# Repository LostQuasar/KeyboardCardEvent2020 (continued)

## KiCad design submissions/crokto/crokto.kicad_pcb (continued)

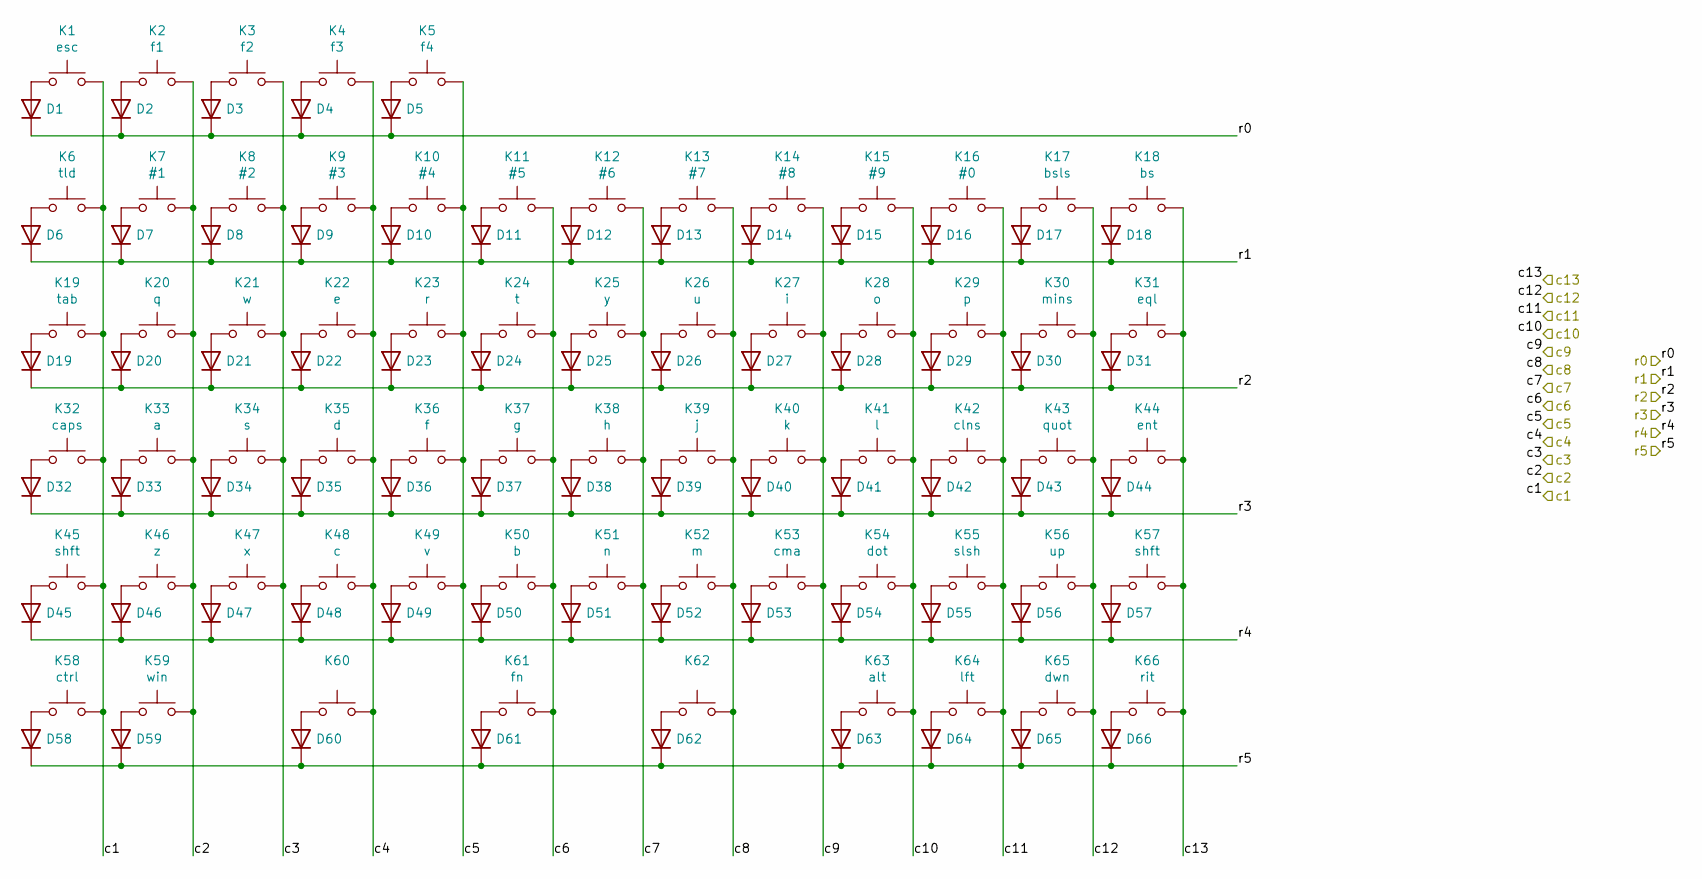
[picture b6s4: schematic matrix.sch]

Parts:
D1, D2, D3, D4, D5, D6, D7, D8, D9, D10, D11, D12, D13, D14, D15, D16, D17, D18, D19, D20, D21, D22, D23, D24, D25, D26, D27, D28, D29, D30, D31, D32, D33, D34, D35, D36, D37, D38, D39, D40, D41, D42, D43, D44, D45, D46, D47, D48, D49, D50, D51, D52, D53, D54, D55, D56, D57, D58, D59, D60, D61, D62, D63, D64, D65, D66: D; D_SOD-323F-VIA; lcsc C2128
K1: esc; 100; lcsc C318887
K2: f1; 100; lcsc C318887
K3: f2; 100; lcsc C318887
K4: f3; 100; lcsc C318887
K5: f4; 100; lcsc C318887
K6: tld; 100; lcsc C318887
K7: #1; 100; lcsc C318887
K8: #2; 100; lcsc C318887
K9: #3; 100; lcsc C318887
K10: #4; 100; lcsc C318887
K11: #5; 100; lcsc C318887
K12: #6; 100; lcsc C318887
K13: #7; 100; lcsc C318887
K14: #8; 100; lcsc C318887
K15: #9; 100; lcsc C318887
K16: #0; 100; lcsc C318887
K17: bsls; 100; lcsc C318887
K18: bs; 100; lcsc C318887
K19: tab; 100; lcsc C318887
K20: q; 100; lcsc C318887
K21: w; 100; lcsc C318887
K22: e; 100; lcsc C318887
K23: r; 100; lcsc C318887
K24: t; 100; lcsc C318887
K25: y; 100; lcsc C318887
K26: u; 100; lcsc C318887
K27: i; 100; lcsc C318887
K28: o; 100; lcsc C318887
K29: p; 100; lcsc C318887
K30: mins; 100; lcsc C318887
K31: eql; 100; lcsc C318887
K32: caps; 100; lcsc C318887
K33: a; 100; lcsc C318887
K34: s; 100; lcsc C318887
K35: d; 100; lcsc C318887
K36: f; 100; lcsc C318887
K37: g; 100; lcsc C318887
K38: h; 100; lcsc C318887
K39: j; 100; lcsc C318887
K40: k; 100; lcsc C318887
K41: l; 100; lcsc C318887
K42: clns; 100; lcsc C318887
K43: quot; 100; lcsc C318887
K44: ent; 100; lcsc C318887
K45, K57: shft; 100; lcsc C318887
K46: z; 100; lcsc C318887
K47: x; 100; lcsc C318887
K48: c; 100; lcsc C318887
K49: v; 100; lcsc C318887
K50: b; 100; lcsc C318887
K51: n; 100; lcsc C318887
K52: m; 100; lcsc C318887
K53: cma; 100; lcsc C318887
K54: dot; 100; lcsc C318887
K55: slsh; 100; lcsc C318887
K56: up; 100; lcsc C318887
K58: ctrl; 100; lcsc C318887
K59: win; 150; lcsc C318887
K60, K62: 200; lcsc C318887
K61: fn; 200; lcsc C318887
K63: alt; 150; lcsc C318887
K64: lft; 100; lcsc C318887
K65: dwn; 100; lcsc C318887
K66: rit; 100; lcsc C318887

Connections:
/16u2/B1: K18.2, K31.2, K44.2, K57.2, K66.2; also elsewhere on the board
/16u2/B2: K12.2, K25.2, K38.2, K51.2; also elsewhere on the board
/16u2/B3: K11.2, K24.2, K37.2, K50.2, K61.2; also elsewhere on the board
/16u2/B4: K5.2, K10.2, K23.2, K36.2, K49.2; also elsewhere on the board
/16u2/B5: K4.2, K9.2, K22.2, K35.2, K48.2, K60.2; also elsewhere on the board
/16u2/B6: K3.2, K8.2, K21.2, K34.2, K47.2; also elsewhere on the board
/16u2/B7: K2.2, K7.2, K20.2, K33.2, K46.2, K59.2; also elsewhere on the board
/16u2/C2: K15.2, K28.2, K41.2, K54.2, K63.2; also elsewhere on the board
/16u2/C4: K14.2, K27.2, K40.2, K53.2; also elsewhere on the board
/16u2/C5: K13.2, K26.2, K39.2, K52.2, K62.2; also elsewhere on the board
/16u2/C6: D1.1 (K), D2.1 (K), D3.1 (K), D4.1 (K), D5.1 (K); also elsewhere on the board
/16u2/C7: K1.2, K6.2, K19.2, K32.2, K45.2, K58.2; also elsewhere on the board
/16u2/D0: K16.2, K29.2, K42.2, K55.2, K64.2; also elsewhere on the board
/16u2/D1: K17.2, K30.2, K43.2, K56.2, K65.2; also elsewhere on the board
/16u2/D2: D6.1 (K), D7.1 (K), D8.1 (K), D9.1 (K), D10.1 (K), D11.1 (K), D12.1 (K), D13.1 (K), D14.1 (K), D15.1 (K), D16.1 (K), D17.1 (K), D18.1 (K); also elsewhere on the board
/16u2/D3: D19.1 (K), D20.1 (K), D21.1 (K), D22.1 (K), D23.1 (K), D24.1 (K), D25.1 (K), D26.1 (K), D27.1 (K), D28.1 (K), D29.1 (K), D30.1 (K), D31.1 (K); also elsewhere on the board
/16u2/D4: D32.1 (K), D33.1 (K), D34.1 (K), D35.1 (K), D36.1 (K), D37.1 (K), D38.1 (K), D39.1 (K), D40.1 (K), D41.1 (K), D42.1 (K), D43.1 (K), D44.1 (K); also elsewhere on the board
/16u2/D5: D45.1 (K), D46.1 (K), D47.1 (K), D48.1 (K), D49.1 (K), D50.1 (K), D51.1 (K), D52.1 (K), D53.1 (K), D54.1 (K), D55.1 (K), D56.1 (K), D57.1 (K); also elsewhere on the board
/16u2/D6: D58.1 (K), D59.1 (K), D60.1 (K), D61.1 (K), D62.1 (K), D63.1 (K), D64.1 (K), D65.1 (K), D66.1 (K); also elsewhere on the board
unnamed: D1.2 (A), K1.1
unnamed: D2.2 (A), K2.1
unnamed: D3.2 (A), K3.1
unnamed: D4.2 (A), K4.1
unnamed: D5.2 (A), K5.1
unnamed: D6.2 (A), K6.1
unnamed: D7.2 (A), K7.1
unnamed: D8.2 (A), K8.1
unnamed: D9.2 (A), K9.1
unnamed: D10.2 (A), K10.1
unnamed: D11.2 (A), K11.1
unnamed: D12.2 (A), K12.1
unnamed: D13.2 (A), K13.1
unnamed: D14.2 (A), K14.1
unnamed: D15.2 (A), K15.1
unnamed: D16.2 (A), K16.1
unnamed: D17.2 (A), K17.1
unnamed: D18.2 (A), K18.1
unnamed: D19.2 (A), K19.1
unnamed: D20.2 (A), K20.1
unnamed: D21.2 (A), K21.1
unnamed: D22.2 (A), K22.1
unnamed: D23.2 (A), K23.1
unnamed: D24.2 (A), K24.1
unnamed: D25.2 (A), K25.1
unnamed: D26.2 (A), K26.1
unnamed: D27.2 (A), K27.1
unnamed: D28.2 (A), K28.1
unnamed: D29.2 (A), K29.1
unnamed: D30.2 (A), K30.1
unnamed: D31.2 (A), K31.1
unnamed: D32.2 (A), K32.1
unnamed: D33.2 (A), K33.1
unnamed: D34.2 (A), K34.1
unnamed: D35.2 (A), K35.1
unnamed: D36.2 (A), K36.1
unnamed: D37.2 (A), K37.1
unnamed: D38.2 (A), K38.1
unnamed: D39.2 (A), K39.1
unnamed: D40.2 (A), K40.1
unnamed: D41.2 (A), K41.1
unnamed: D42.2 (A), K42.1
unnamed: D43.2 (A), K43.1
unnamed: D44.2 (A), K44.1
unnamed: D45.2 (A), K45.1
unnamed: D46.2 (A), K46.1
unnamed: D47.2 (A), K47.1
unnamed: D48.2 (A), K48.1
unnamed: D49.2 (A), K49.1
unnamed: D50.2 (A), K50.1
unnamed: D51.2 (A), K51.1
unnamed: D52.2 (A), K52.1
unnamed: D53.2 (A), K53.1
unnamed: D54.2 (A), K54.1
unnamed: D55.2 (A), K55.1
unnamed: D56.2 (A), K56.1
unnamed: D57.2 (A), K57.1
unnamed: D58.2 (A), K58.1
unnamed: D59.2 (A), K59.1
unnamed: D60.2 (A), K60.1
unnamed: D61.2 (A), K61.1
unnamed: D62.2 (A), K62.1
unnamed: D63.2 (A), K63.1
unnamed: D64.2 (A), K64.1
unnamed: D65.2 (A), K65.1
unnamed: D66.2 (A), K66.1

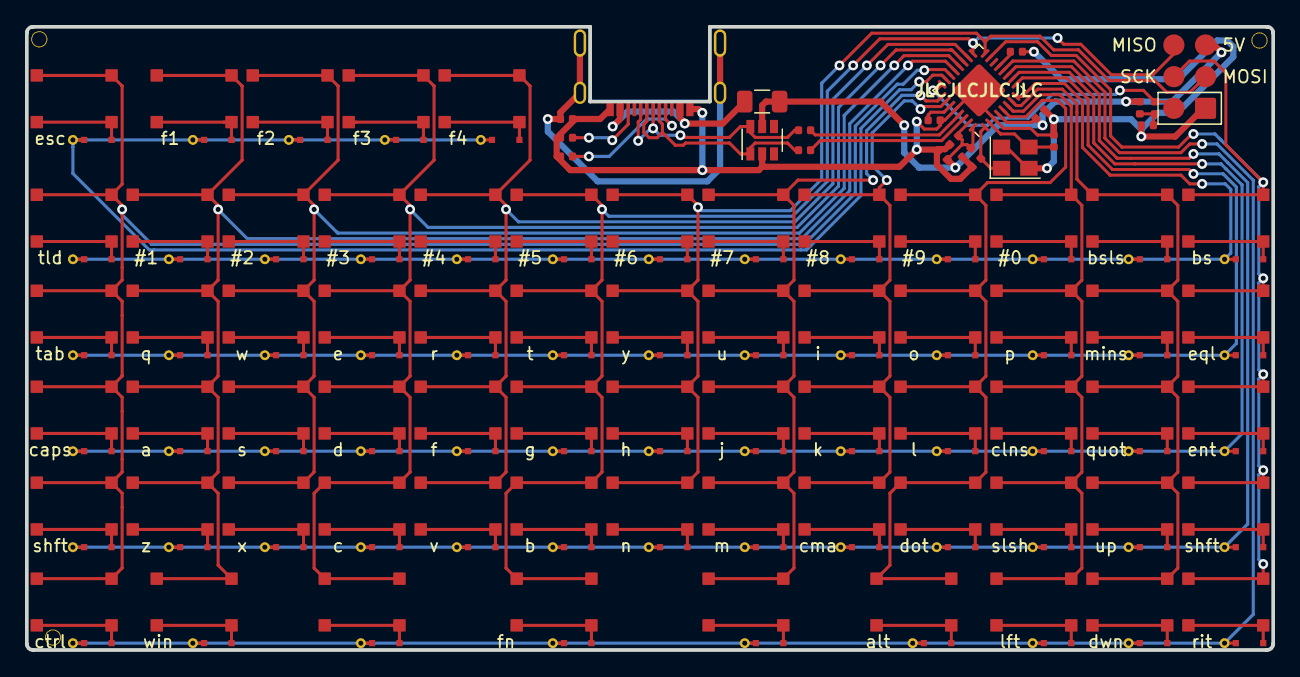
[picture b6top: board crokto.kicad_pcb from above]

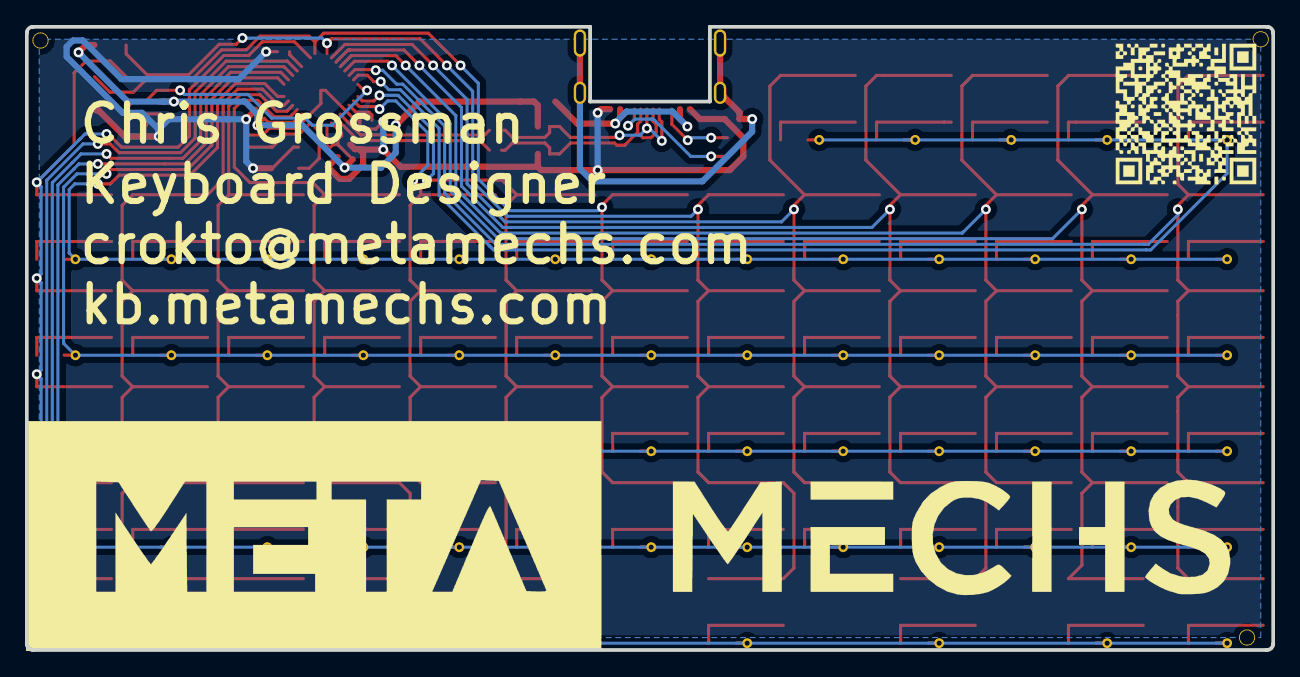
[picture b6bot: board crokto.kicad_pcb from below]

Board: 2 copper layers, 100.0 x 50.0 mm, 160 parts (2 on the bottom side), 101 nets.

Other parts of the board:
C1: 10u; C_0402_1005Metric
C2, C3, C4, C8: 100n; C_0402_1005Metric
C5, C6: 10pf; C_0402_1005Metric
C7: 1u; C_0402_1005Metric
H3: jlc
H4, H5, H6: jlc; JLCPCBA
J1: AVR-ISP-6; 2x3-jumper
R1, R2: 22; R_0402_1005Metric
R3: 4.7K; R_0402_1005Metric
R4: 330; R_0402_1005Metric
R5: 10k; R_0402_1005Metric
U1: ATmega16U2-MU; QFN-32-1EP_5x5mm_P0.5mm_EP3.1x3.1mm
Y1: Crystal_GND24; Crystal_SMD_3225-4Pin_3.2x2.5mm

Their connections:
+5V: C1.1, C2.1, C3.1, C4.1, J1.2, R3.2, U1.4, U1.31, U1.32; also elsewhere on the board
/16u2/B1: J1.3, U1.15; also elsewhere on the board
/16u2/B2: J1.4, U1.16; also elsewhere on the board
/16u2/B3: J1.1, U1.17; also elsewhere on the board
/16u2/B4: U1.18; also elsewhere on the board
/16u2/B5: U1.19; also elsewhere on the board
/16u2/B6: U1.20; also elsewhere on the board
/16u2/B7: U1.21; also elsewhere on the board
/16u2/C2: U1.5; also elsewhere on the board
/16u2/C4: U1.26; also elsewhere on the board
/16u2/C5: U1.25; also elsewhere on the board
/16u2/C6: U1.23; also elsewhere on the board
/16u2/C7: U1.22; also elsewhere on the board
/16u2/D0: U1.6; also elsewhere on the board
/16u2/D1: U1.7; also elsewhere on the board
/16u2/D2: U1.8; also elsewhere on the board
/16u2/D3: U1.9; also elsewhere on the board
/16u2/D4: U1.10; also elsewhere on the board
/16u2/D5: U1.11; also elsewhere on the board
/16u2/D6: U1.12; also elsewhere on the board
/16u2/D+: R1.1, U1.29
/16u2/D-: R2.2, U1.30
/16u2/DB+: R1.2; also elsewhere on the board
/16u2/DB-: R2.1; also elsewhere on the board
/16u2/RST: J1.5, R4.2, U1.24
GND: C1.2, C2.2, C3.2, C4.2, C5.2, C6.2, C7.2, C8.2, J1.6, R5.2, U1.3, U1.28, U1.33, Y1.2, Y1.4; also elsewhere on the board
unnamed: C5.1, U1.1, Y1.1
unnamed: C6.1, U1.2, Y1.3
unnamed: C7.1, U1.27
unnamed: C8.1, R3.1, R4.1
unnamed: R5.1, U1.13

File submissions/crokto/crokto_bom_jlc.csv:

"Comment","Designator","Footprint","LCSC Part #"
"10u","C1","C_0402_1005Metric","C15525"
"100n","C2,C3,C4,C8","C_0402_1005Metric","C1525"
"10pf","C5,C6","C_0402_1005Metric","C32949"
"1u","C7","C_0402_1005Metric","C52923"
"D","D6,D19,D32,D45,D58,D7,D20,D33,D46,D59,D8,D21,D34,D47,D9,D22,D35,D48,D60,D10,D23,D36,D49,D11,D24,D37,D50,D61,D12,D25,D38,D51,D13,D26,D39,D52,D62,D14,D27,D40,D53,D15,D28,D41,D54,D63,D16,D29,D42,D55,D64,D17,D30,D43,D56,D65,D18,D31,D44,D57,D66,D1,D2,D3,D4,D5","D_SOD-323F-VIA","C2128"
"esc","K1","100","C318887"
"f1","K2","100","C318887"
"f2","K3","100","C318887"
"f3","K4","100","C318887"
"f4","K5","100","C318887"
"tld","K6","100","C318887"
"#1","K7","100","C318887"
"#2","K8","100","C318887"
"#3","K9","100","C318887"
"#4","K10","100","C318887"
"#5","K11","100","C318887"
"#6","K12","100","C318887"
"#7","K13","100","C318887"
"#8","K14","100","C318887"
"#9","K15","100","C318887"
"#0","K16","100","C318887"
"bsls","K17","100","C318887"
"bs","K18","100","C318887"
"tab","K19","100","C318887"
"q","K20","100","C318887"
"w","K21","100","C318887"
"e","K22","100","C318887"
"r","K23","100","C318887"
"t","K24","100","C318887"
"y","K25","100","C318887"
"u","K26","100","C318887"
"i","K27","100","C318887"
"o","K28","100","C318887"
"p","K29","100","C318887"
"mins","K30","100","C318887"
"eql","K31","100","C318887"
"caps","K32","100","C318887"
"a","K33","100","C318887"
"s","K34","100","C318887"
"d","K35","100","C318887"
"f","K36","100","C318887"
"g","K37","100","C318887"
"h","K38","100","C318887"
"j","K39","100","C318887"
"k","K40","100","C318887"
"l","K41","100","C318887"
"clns","K42","100","C318887"
"quot","K43","100","C318887"
"ent","K44","100","C318887"
"shft","K45,K57","100","C318887"
"z","K46","100","C318887"
"x","K47","100","C318887"
"c","K48","100","C318887"
"v","K49","100","C318887"
"b","K50","100","C318887"
"n","K51","100","C318887"
"m","K52","100","C318887"
"cma","K53","100","C318887"
"dot","K54","100","C318887"
"slsh","K55","100","C318887"
"up","K56","100","C318887"
"ctrl","K58","100","C318887"
"win","K59","150","C318887"
"","K60,K62","200","C318887"
"fn","K61","200","C318887"
"alt","K63","150","C318887"
"lft","K64","100","C318887"
"dwn","K65","100","C318887"
"rit","K66","100","C318887"
"PTC","PTC1","Fuse_1206_3216Metric","C70076"
"22","R1,R2","R_0402_1005Metric","C25092"
"4.7K","R3","R_0402_1005Metric","C25900"
"330","R4","R_0402_1005Metric","C25890"
"10k","R5","R_0402_1005Metric","C25744"
"5.1k","R7,R8","R_0402_1005Metric","C25905"
"0","R9","R_0402_1005Metric","C25905"
"ATmega16U2-MU","U1","QFN-32-1EP_5x5mm_P0.5mm_EP3.1x3.1mm","C17317"
"SRV05-4","U2","SOT-23-6","C85364"
"Crystal_GND24","Y1","Crystal_SMD_3225-4Pin_3.2x2.5mm","C13738"

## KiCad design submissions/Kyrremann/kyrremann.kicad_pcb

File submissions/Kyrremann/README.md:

# Kyrremann's Business card

This is my business card aka the keychuks! The keyboard can be split in two, and connected with 6 individual wires to
form a split board, or used as nunchuks when you're bored.

The inital idea was to try my hands at a split board, but the size made it a bit too hard for me, so instead I went
with something between. Where you can split it, but you have to make your own 6 pin wire, and solder it.

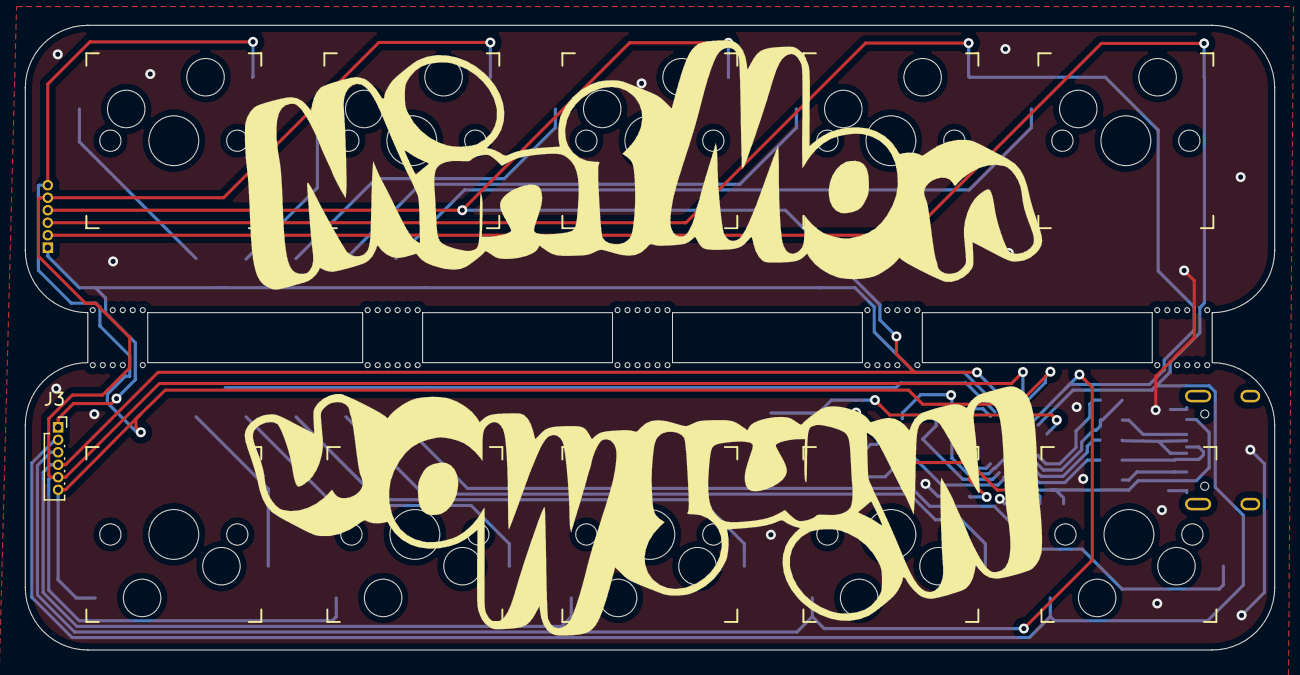
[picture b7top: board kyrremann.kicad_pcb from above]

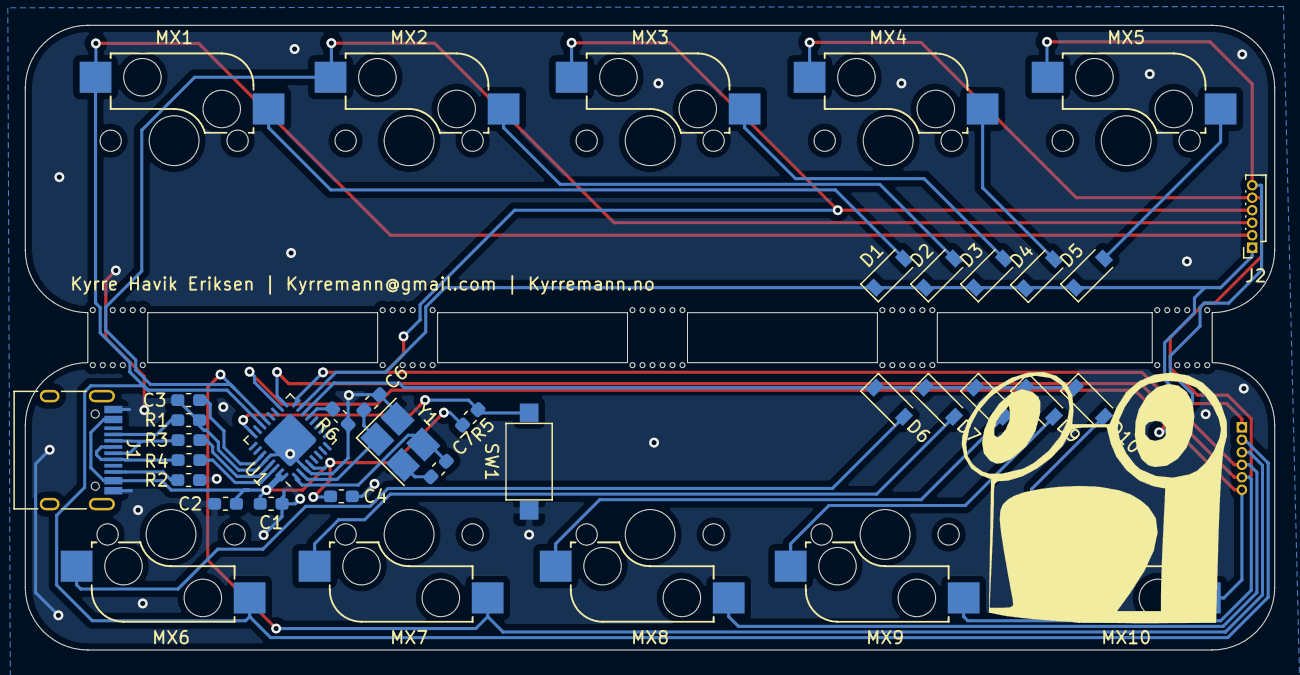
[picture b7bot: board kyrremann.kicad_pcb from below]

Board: 2 copper layers, 100.0 x 50.0 mm, 38 parts (27 on the bottom side), 30 nets.

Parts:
C1, C2, C3: 1uF; C_0603_1608Metric_Pad1.05x0.95mm_HandSolder
C4: 0.1uF; C_0603_1608Metric_Pad1.05x0.95mm_HandSolder
C6, C7: 14pF; C_0603_1608Metric_Pad1.05x0.95mm_HandSolder
D1, D2, D3, D4, D5, D6, D7, D8, D9, D10: D; D_SOD-123
J1: USB_C_Receptacle_USB2.0; USB_C_Receptacle_HRO_TYPE-C-31-M-12
J2, J3: Conn_01x06_Female; PinSocket_1x06_P1.00mm_Vertical
MX1, MX2, MX3, MX4, MX5, MX6, MX7, MX8, MX9, MX10: MX-NoLED; Kailh_socket_MX
R1, R2: 5.1K; R_0603_1608Metric_Pad1.05x0.95mm_HandSolder
R3, R4: 22; R_0603_1608Metric_Pad1.05x0.95mm_HandSolder
R5, R6: 10K; R_0603_1608Metric_Pad1.05x0.95mm_HandSolder
SW1: SW_Push; SW_SPST_CK_RS282G05A3
U1: ATmega32U2-MU; QFN-32-1EP_5x5mm_P0.5mm_EP3.1x3.1mm
Y1: 16Mhz; Crystal_SMD_3225-4Pin_3.2x2.5mm_HandSoldering

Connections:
/+5v: C1.1, C2.1, C4.1, J1.A4, J1.A9, J1.B4, J1.B9, R5.2, U1.4, U1.31, U1.32
/COL00: J2.2, J3.2, MX1.1, MX6.1, U1.22
/COL01: J2.3, J3.3, MX2.1, MX7.1, U1.21
/COL02: J2.4, J3.4, MX3.1, MX8.1, U1.16
/COL03: J2.5, J3.5, MX4.1, MX9.1, U1.17
/COL04: J2.6, J3.6, MX5.1, MX10.1, U1.18
/D+: J1.A6, J1.B6, R4.1
/D-: J1.A7, J1.B7, R3.2
/RESET: R5.1, SW1.1, U1.24
/ROW0: D1.1, D2.1, D3.1, D4.1, D5.1, J2.1, J3.1, U1.15
/ROW1: D6.1, D7.1, D8.1, D9.1, D10.1, U1.14
/UCAP: C3.1, U1.27
/XTAL1: C7.1, U1.1, Y1.3
/XTAL2: C6.1, U1.2, Y1.1
GND: C1.2, C2.2, C3.2, C4.2, C6.2, C7.2, J1.A1, J1.A12, J1.B1, J1.B12, R1.1, R2.2, R6.1, SW1.2, U1.3, U1.28, U1.33, Y1.2, Y1.4
unnamed: D1.2, MX1.2
unnamed: D2.2, MX2.2
unnamed: D3.2, MX3.2
unnamed: D4.2, MX4.2
unnamed: D5.2, MX5.2
unnamed: D6.2, MX6.2
unnamed: D7.2, MX7.2
unnamed: D8.2, MX8.2
unnamed: D9.2, MX9.2
unnamed: D10.2, MX10.2
unnamed: J1.A5, R1.2
unnamed: J1.B5, R2.1
unnamed: R3.1, U1.29
unnamed: R4.2, U1.30
unnamed: R6.2, U1.13

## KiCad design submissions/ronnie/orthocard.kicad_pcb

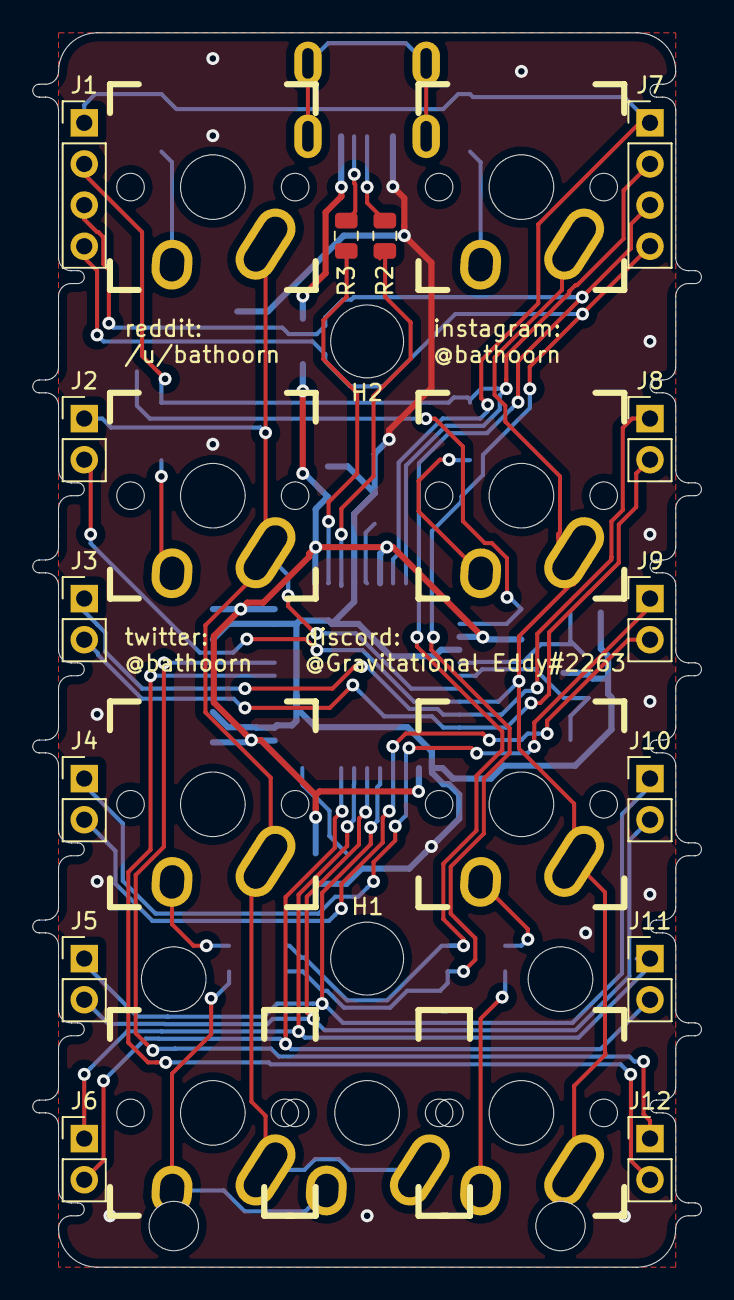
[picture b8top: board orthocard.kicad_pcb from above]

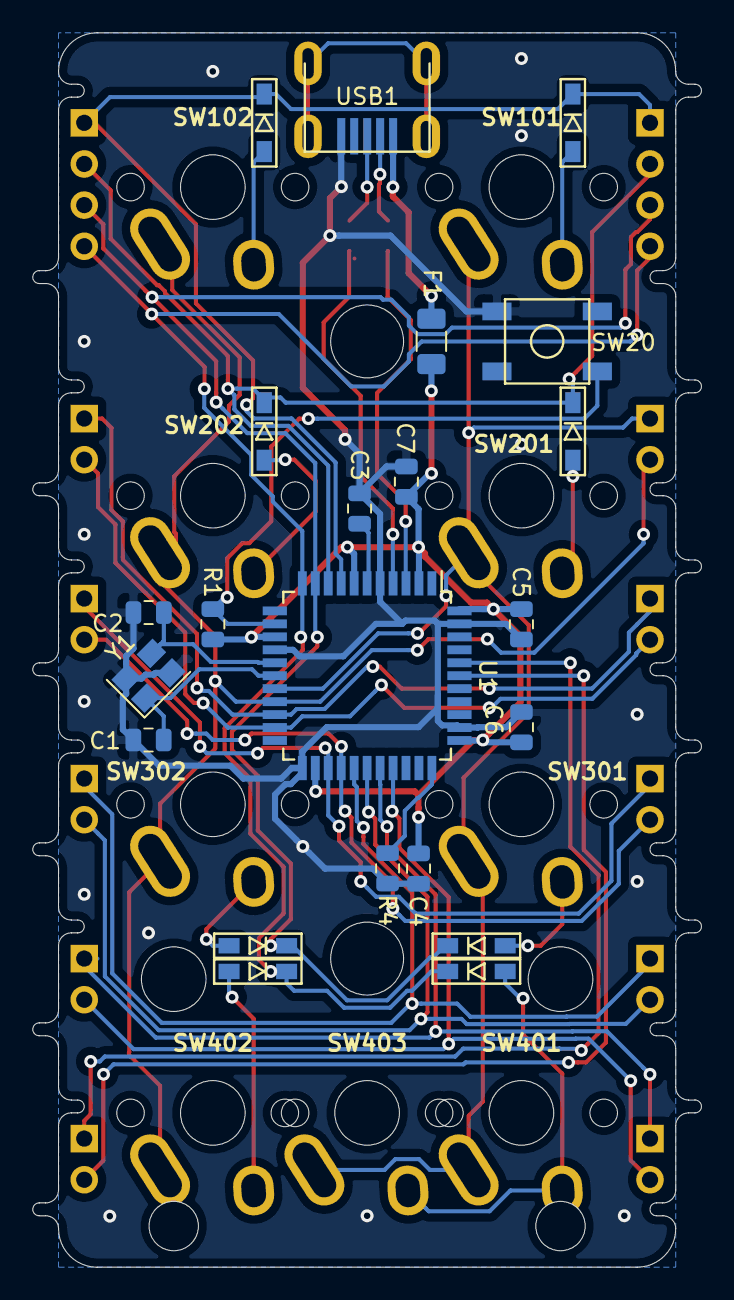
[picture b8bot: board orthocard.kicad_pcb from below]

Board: 2 copper layers, 41.3 x 76.2 mm, 47 parts (14 on the bottom side), 36 nets.

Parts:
C1, C2: 22pF; C_0805_2012Metric
C3: 1uF; C_0805_2012Metric
C4, C5, C6: 0.1uF; C_0805_2012Metric
C7: 10uF; C_0805_2012Metric
D101, D102, D201, D202, D301, D302, D401, D402: D; D3_SMD_Back
F1: 500mA; Fuse_1206_3216Metric
H1, H2: MountingHole; MountingHole_4.5mm
J1, J7: Conn_01x04; PinHeader_1x04_P2.54mm_Vertical
J2, J3, J4, J5, J6, J8, J9, J10, J11, J12: Conn_01x02; PinHeader_1x02_P2.54mm_Vertical
R1, R4: 10k; R_0805_2012Metric
R2, R3: 22; R_0805_2012Metric
SW20: SW_Push; SKQG-1155865
SW101, SW102, SW201, SW202, SW301, SW302, SW401, SW402: SW_PUSH; Mx_Alps_100
SW403: SW_PUSH; Mx_Alps_200
U1: ATmega32U4-AU; TQFP-44_10x10mm_P0.8mm
USB1: Molex-0548190589; Molex-0548190589-fixed
Y1: 16MHz; Crystal_SMD_3225-4Pin_3.2x2.5mm

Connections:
+5V: C4.1, C5.1, C6.1, C7.1, F1.1, R1.1, U1.2, U1.7, U1.14, U1.24, U1.34, U1.44
D+: R2.2, USB1.3
D-: R3.2, USB1.4
GND: C1.2, C2.2, C3.2, C4.2, C5.2, C6.2, C7.2, R4.1, SW20.1, U1.5, U1.15, U1.23, U1.35, U1.43, USB1.1, Y1.2, Y1.4
unnamed: C1.1, U1.17, Y1.1
unnamed: C2.1, U1.16, Y1.3
unnamed: C3.1, U1.6
unnamed: D101.2, SW101.2
unnamed: D102.2, SW102.2
unnamed: D201.2, SW201.2
unnamed: D202.2, SW202.2
unnamed: D301.2, SW301.2
unnamed: D302.2, SW302.2
unnamed: D401.2, SW401.2, SW403.2
unnamed: D402.2, SW402.2
unnamed: R1.2, SW20.2, U1.13
unnamed: R2.1, U1.4
unnamed: R3.1, U1.3
unnamed: R4.2, U1.33
VCC: F1.2, USB1.5
col01: J2.1, SW101.1, SW201.1, SW301.1, SW401.1, SW403.1, U1.18
col02: J2.2, SW102.1, SW202.1, SW302.1, SW402.1, U1.19
col03: J3.1, J8.1, U1.20
col04: J3.2, J8.2, U1.21
col05: J4.1, J9.1, U1.25
col06: J4.2, J9.2, U1.26
col07: J5.1, J10.1, U1.27
col08: J5.2, J10.2, U1.28
col09: J6.1, J11.1, U1.29
col10: J6.2, J11.2, U1.30
col11: J12.1, U1.40
col12: J12.2, U1.39
row01: D101.1, D102.1, J1.1, J7.1, U1.8
row02: D201.1, D202.1, J1.2, J7.2, U1.9
row03: D301.1, D302.1, J1.3, J7.3, U1.10
row04: D401.1, D402.1, J1.4, J7.4, U1.11

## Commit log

2019-10-01 Create LICENSE
2019-10-01 Rename LICENSE to template/LICENSE
2020-02-29 test commit
2020-04-09 add submission initial version
2020-04-09 md issues
2020-04-09 Initial build
    Initial build in Kicad to get feedback.
2020-04-10 adding Flying_MX
2020-04-10 updating readme
2020-04-10 minor updates
2020-04-10 editing rear silk
2020-04-11 changing routing
2020-04-11 adding GND fill
2020-04-11 updating images
2020-04-11 minor update
2020-04-11 updating gerber
2020-04-11 cleaning up license
2020-04-11 random_bytes first version
2020-04-11 host images on imgur
2020-04-13 Remove images
2020-04-15 mostly done already
2020-04-17 attempting to make a usb c version
2020-04-17 moving things around a bit
2020-04-17 correcting & improving some things
2020-04-17 updating gerber and images
2020-04-23 updating footprints and silk
2020-04-24 removing images
2020-04-26 Add submission
2020-04-26 - added libraries - added pictures - added more documentation to the README.md - added credits
2020-04-26 - moved images to Imgur
2020-04-26 - deleted all unused footprints
2020-04-26 Add files for design review
2020-04-30 made some changes based on spacemans review - added a note on the usb connector in the readme.md - created some room around a mounting hole so the traces don't come to close - removed some hanging tr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
2020-05-02 My submission for the cool competition
2020-05-02 Forgot a space in the header
2020-05-03 Remove Keebio.pretty + images
2020-05-04 Update readme.md
    Add correct image URLs
2020-05-07 dkudriavtsev's submission
2020-05-07 Added README.md
2020-05-12 added all the not fun stuff
2020-05-16 a-chol: fix usb-c connector connections and add some artworks.
2020-05-18 Retraced the keyboard, and added cool silks
2020-05-18 removing unecassary files
2020-05-27 Update files
2020-05-27 Fix markdown images
2020-05-27 Add video
2020-05-27 Remove fp-info-cache from template
2020-05-28 switched design entirely lol
2020-05-28 added readme, cleaned up
2020-05-29 removed images
2020-05-29 fixed footprints, added jlcpcba
2020-05-29 Final Submission
    Made some changes to the routing, added some ground fills, and added some decorative slkscreen.
2020-05-29 Fixed imgur embeds
    Changed link text to hopefully fix embedded images.
2020-05-31 Initial project files
